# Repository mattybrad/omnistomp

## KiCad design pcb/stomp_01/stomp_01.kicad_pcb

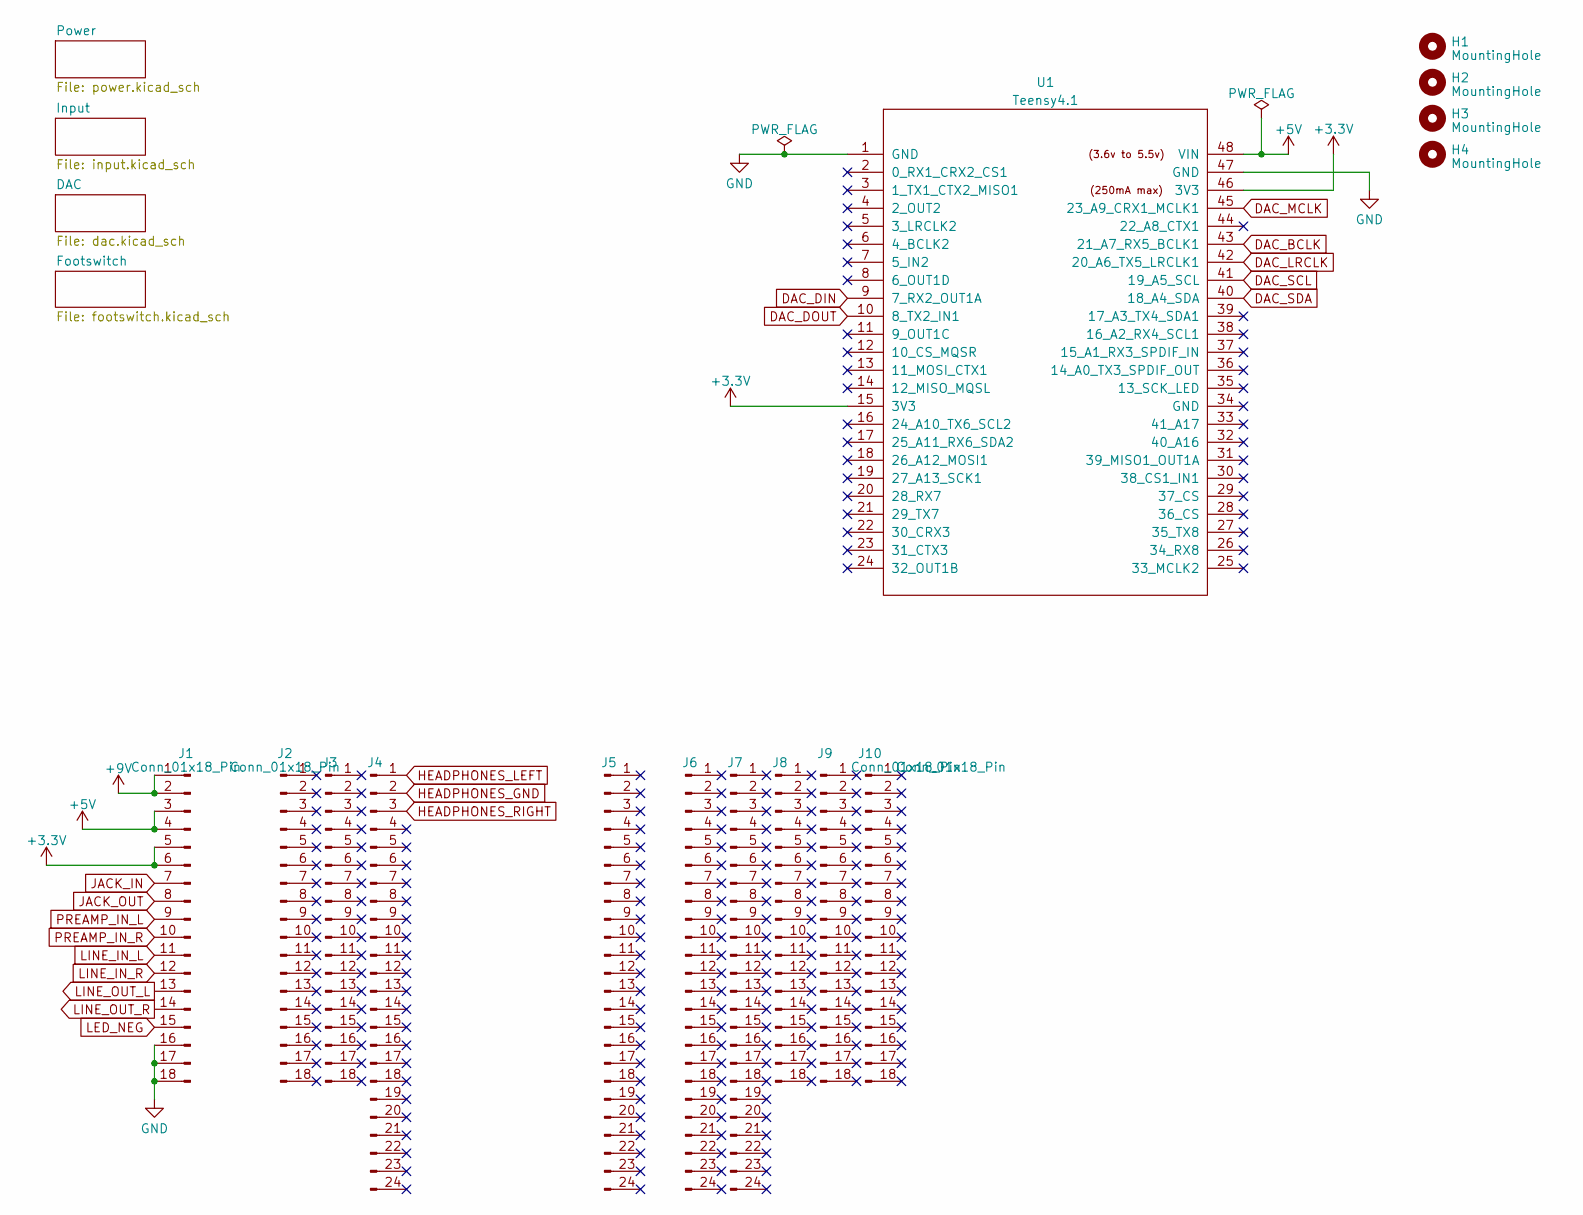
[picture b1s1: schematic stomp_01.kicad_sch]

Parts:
H1, H2, H3, H4: MountingHole; MountingHole_3.2mm_M3
J1, J2, J3, J8, J9, J10: Conn_01x18_Pin; PinHeader_1x18_P2.54mm_Vertical_perf
J4, J5, J6, J7: Conn_01x18_Pin; PinHeader_1x24_P2.54mm_Vertical_perf
U1: Teensy4.1; Teensy41_stomp

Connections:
+3.3V: J1.5, J1.6, U1.15 (3V3), U1.46 (3V3); also elsewhere on the board
+5V: J1.3, J1.4, U1.48 (VIN); also elsewhere on the board
+9V: J1.1, J1.2; also elsewhere on the board
DAC_BCLK: U1.43 (21_A7_RX5_BCLK1); also elsewhere on the board
DAC_DIN: U1.9 (7_RX2_OUT1A); also elsewhere on the board
DAC_DOUT: U1.10 (8_TX2_IN1); also elsewhere on the board
DAC_LRCLK: U1.42 (20_A6_TX5_LRCLK1); also elsewhere on the board
DAC_MCLK: U1.45 (23_A9_CRX1_MCLK1); also elsewhere on the board
DAC_SCL: U1.41 (19_A5_SCL); also elsewhere on the board
DAC_SDA: U1.40 (18_A4_SDA); also elsewhere on the board
GND: J1.16, J1.17, J1.18, U1.1 (GND), U1.47 (GND); also elsewhere on the board
HEADPHONES_GND: J4.2; also elsewhere on the board
HEADPHONES_LEFT: J4.1; also elsewhere on the board
HEADPHONES_RIGHT: J4.3; also elsewhere on the board
JACK_IN: J1.7; also elsewhere on the board
JACK_OUT: J1.8; also elsewhere on the board
LED_NEG: J1.15; also elsewhere on the board
LINE_IN_L: J1.11; also elsewhere on the board
LINE_IN_R: J1.12; also elsewhere on the board
LINE_OUT_L: J1.13; also elsewhere on the board
LINE_OUT_R: J1.14; also elsewhere on the board
PREAMP_IN_L: J1.9; also elsewhere on the board
PREAMP_IN_R: J1.10; also elsewhere on the board

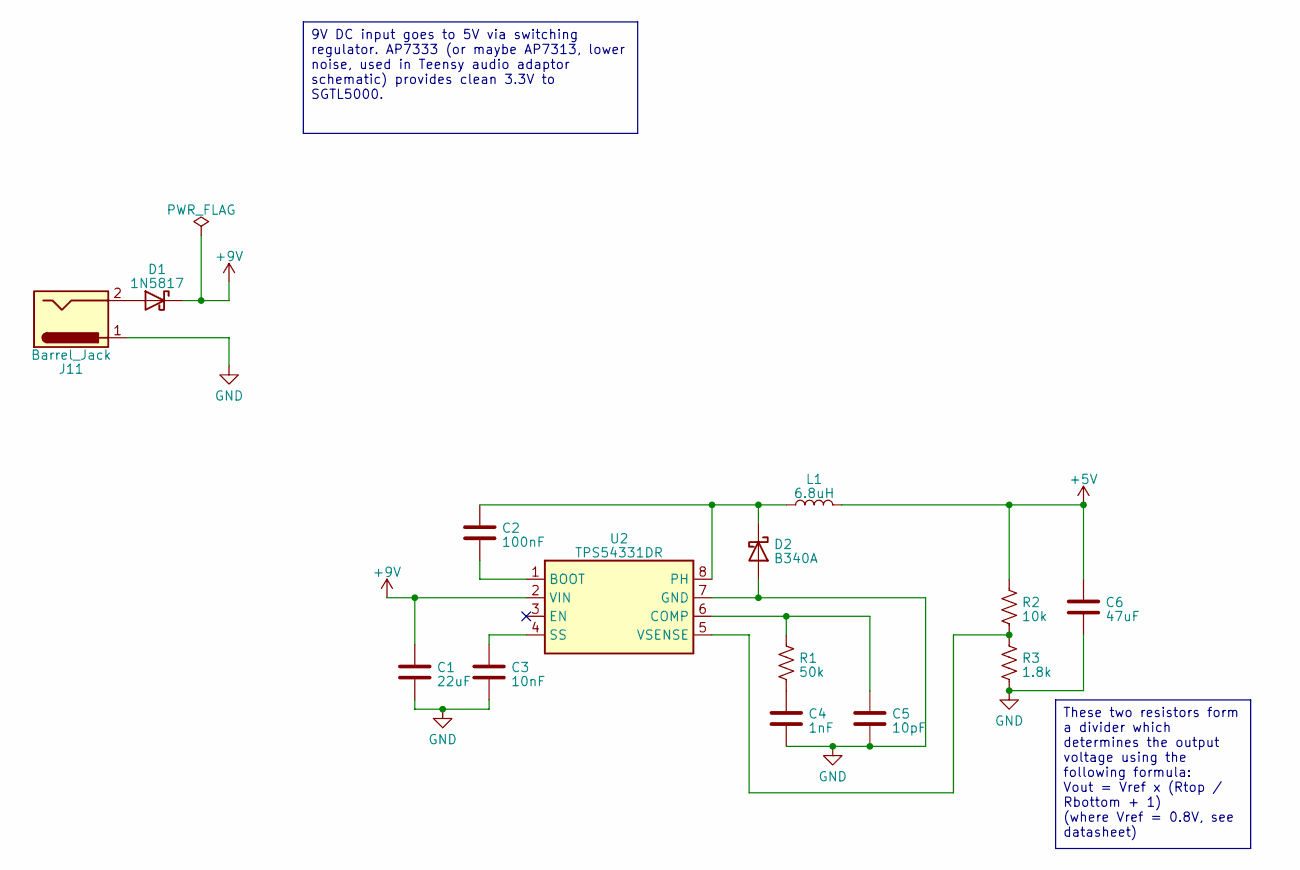
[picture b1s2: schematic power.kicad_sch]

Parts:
C1: 22uF; C_0805_2012Metric
C2: 100nF; C_0603_1608Metric
C3: 10nF; C_0603_1608Metric
C4: 1nF; C_0603_1608Metric
C5: 10pF; C_0603_1608Metric
C6: 47uF; C_1210_3225Metric
D1: 1N5817; D_DO-41_SOD81_P10.16mm_Horizontal
D2: B340A; D_SMA
J11: Barrel_Jack; SolderWire-1sqmm_1x02_P5.4mm_D1.4mm_OD2.7mm
L1: 6.8uH; L_Sunlord_SWPA6045S
R1: 50k; R_0603_1608Metric
R2: 10k; R_0603_1608Metric
R3: 1.8k; R_0603_1608Metric
U2: TPS54331DR; SOIC-8_3.9x4.9mm_P1.27mm

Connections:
+5V: C6.1, L1.2, R2.1; also elsewhere on the board
+9V: C1.1, D1.1 (K), U2.2 (VIN); also elsewhere on the board
GND: C1.2, C3.2, C4.2, C5.2, C6.2, D2.2 (A), J11.1, R3.2, U2.7 (GND); also elsewhere on the board
unnamed: C4.1, R1.2
unnamed: D1.2 (A), J11.2
unnamed: C2.1, D2.1 (K), L1.1, U2.8 (PH)
unnamed: C2.2, U2.1 (BOOT)
unnamed: C5.1, R1.1, U2.6 (COMP)
unnamed: C3.1, U2.4 (SS)
unnamed: R2.2, R3.1, U2.5 (VSENSE)

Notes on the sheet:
9V DC input goes to 5V via switching regulator. AP7333 (or maybe AP7313, lower noise, used in Teensy audio adaptor schematic) provides clean 3.3V to SGTL5000.
These two resistors form a divider which determines the output voltage using the following formula: Vout = Vref x (Rtop / Rbottom + 1) (where Vref = 0.8V, see datasheet)

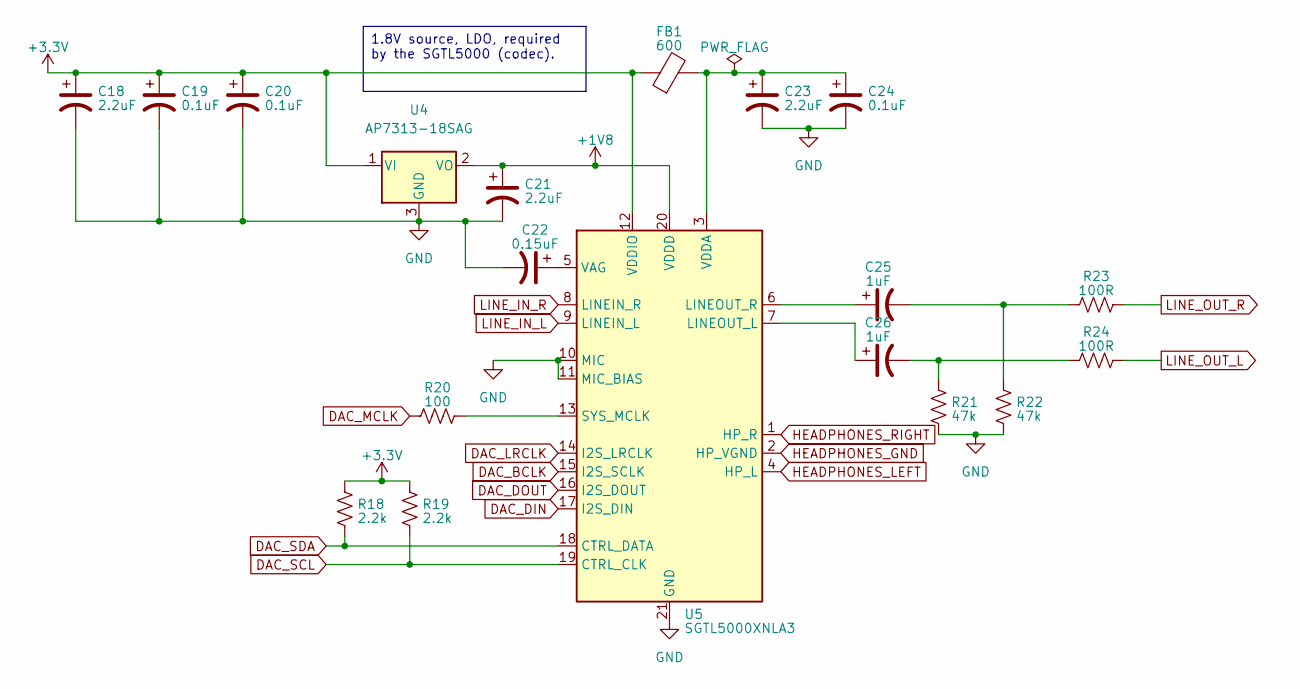
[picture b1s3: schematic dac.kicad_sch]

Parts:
C18, C21, C23: 2.2uF; C_0603_1608Metric
C19, C20, C24: 0.1uF; C_0603_1608Metric
C22: 0.15uF; C_0603_1608Metric
C25, C26: 1uF; C_0603_1608Metric
FB1: 600; L_0603_1608Metric
R18, R19: 2.2k; R_0603_1608Metric
R20: 100; R_0603_1608Metric
R21, R22: 47k; R_0603_1608Metric
R23, R24: 100R; R_0603_1608Metric
U4: AP7313-18SAG; SOT-23
U5: SGTL5000XNLA3; QFN-20-1EP_3x3mm_P0.4mm_EP1.65x1.65mm

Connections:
+1V8: C21.1, U4.2 (VO), U5.20 (VDDD)
+3.3V: C18.1, C19.1, C20.1, FB1.1, R18.2, R19.2, U4.1 (VI), U5.12 (VDDIO); also elsewhere on the board
DAC_BCLK: U5.15 (I2S_SCLK); also elsewhere on the board
DAC_DIN: U5.17 (I2S_DIN); also elsewhere on the board
DAC_DOUT: U5.16 (I2S_DOUT); also elsewhere on the board
DAC_LRCLK: U5.14 (I2S_LRCLK); also elsewhere on the board
DAC_MCLK: R20.2; also elsewhere on the board
DAC_SCL: R19.1, U5.19 (CTRL_CLK); also elsewhere on the board
DAC_SDA: R18.1, U5.18 (CTRL_DATA); also elsewhere on the board
GND: C18.2, C19.2, C20.2, C21.2, C22.2, C23.2, C24.2, R21.1, R22.1, U4.3 (GND), U5.10 (MIC), U5.11 (MIC_BIAS), U5.21 (GND); also elsewhere on the board
HEADPHONES_GND: U5.2 (HP_VGND); also elsewhere on the board
HEADPHONES_LEFT: U5.4 (HP_L); also elsewhere on the board
HEADPHONES_RIGHT: U5.1 (HP_R); also elsewhere on the board
LINE_IN_L: U5.9 (LINEIN_L); also elsewhere on the board
LINE_IN_R: U5.8 (LINEIN_R); also elsewhere on the board
LINE_OUT_L: R24.1; also elsewhere on the board
LINE_OUT_R: R23.1; also elsewhere on the board
unnamed: C25.2, R22.2, R23.2
unnamed: C26.2, R21.2, R24.2
unnamed: C26.1, U5.7 (LINEOUT_L)
unnamed: C25.1, U5.6 (LINEOUT_R)
unnamed: R20.1, U5.13 (SYS_MCLK)
unnamed: C22.1, U5.5 (VAG)
unnamed: C23.1, C24.1, FB1.2, U5.3 (VDDA)

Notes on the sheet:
1.8V source, LDO, required by the SGTL5000 (codec).

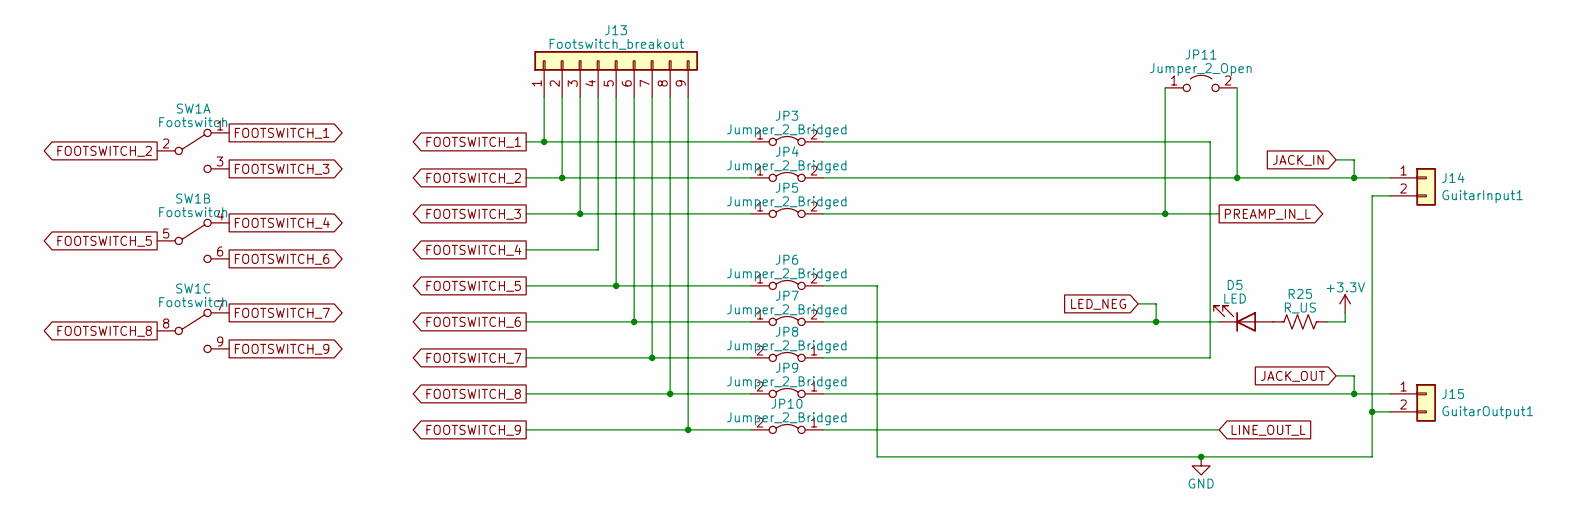
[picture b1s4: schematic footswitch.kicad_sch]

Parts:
D5: LED; LED_D5.0mm
J13: Footswitch_breakout; PinHeader_3x03_P2.54mm_Vertical_footswitch_breakout
J14: GuitarInput1; SolderWire-1sqmm_1x02_P5.4mm_D1.4mm_OD2.7mm
J15: GuitarOutput1; SolderWire-1sqmm_1x02_P5.4mm_D1.4mm_OD2.7mm
JP3, JP4, JP5, JP6, JP7, JP8, JP9, JP10: Jumper_2_Bridged; SolderJumper-2_P1.3mm_Bridged2Bar_RoundedPad1.0x1.5mm
JP11: Jumper_2_Open; SolderJumper-2_P1.3mm_Open_RoundedPad1.0x1.5mm
R25: R_US; R_Axial_DIN0207_L6.3mm_D2.5mm_P7.62mm_Horizontal
SW1: Footswitch; Footswitch_3PDT

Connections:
+3.3V: R25.2; also elsewhere on the board
FOOTSWITCH_1: J13.1, JP3.1 (A), SW1.1 (A)
FOOTSWITCH_2: J13.2, JP4.1 (A), SW1.2 (B)
FOOTSWITCH_3: J13.3, JP5.1 (A), SW1.3 (C)
FOOTSWITCH_4: J13.4, SW1.4 (A)
FOOTSWITCH_5: J13.5, JP6.1 (A), SW1.5 (B)
FOOTSWITCH_6: J13.6, JP7.1 (A), SW1.6 (C)
FOOTSWITCH_7: J13.7, JP8.2 (B), SW1.7 (A)
FOOTSWITCH_8: J13.8, JP9.2 (B), SW1.8 (B)
FOOTSWITCH_9: J13.9, JP10.2 (B), SW1.9 (C)
GND: J14.2, J15.2, JP6.2 (B); also elsewhere on the board
JACK_IN: J14.1, JP4.2 (B), JP11.2 (B); also elsewhere on the board
JACK_OUT: J15.1, JP9.1 (A); also elsewhere on the board
LED_NEG: D5.1 (K), JP7.2 (B); also elsewhere on the board
LINE_OUT_L: JP10.1 (A); also elsewhere on the board
unnamed: D5.2 (A), R25.1
unnamed: JP3.2 (B), JP8.1 (A)
PREAMP_IN_L: JP5.2 (B), JP11.1 (A); also elsewhere on the board

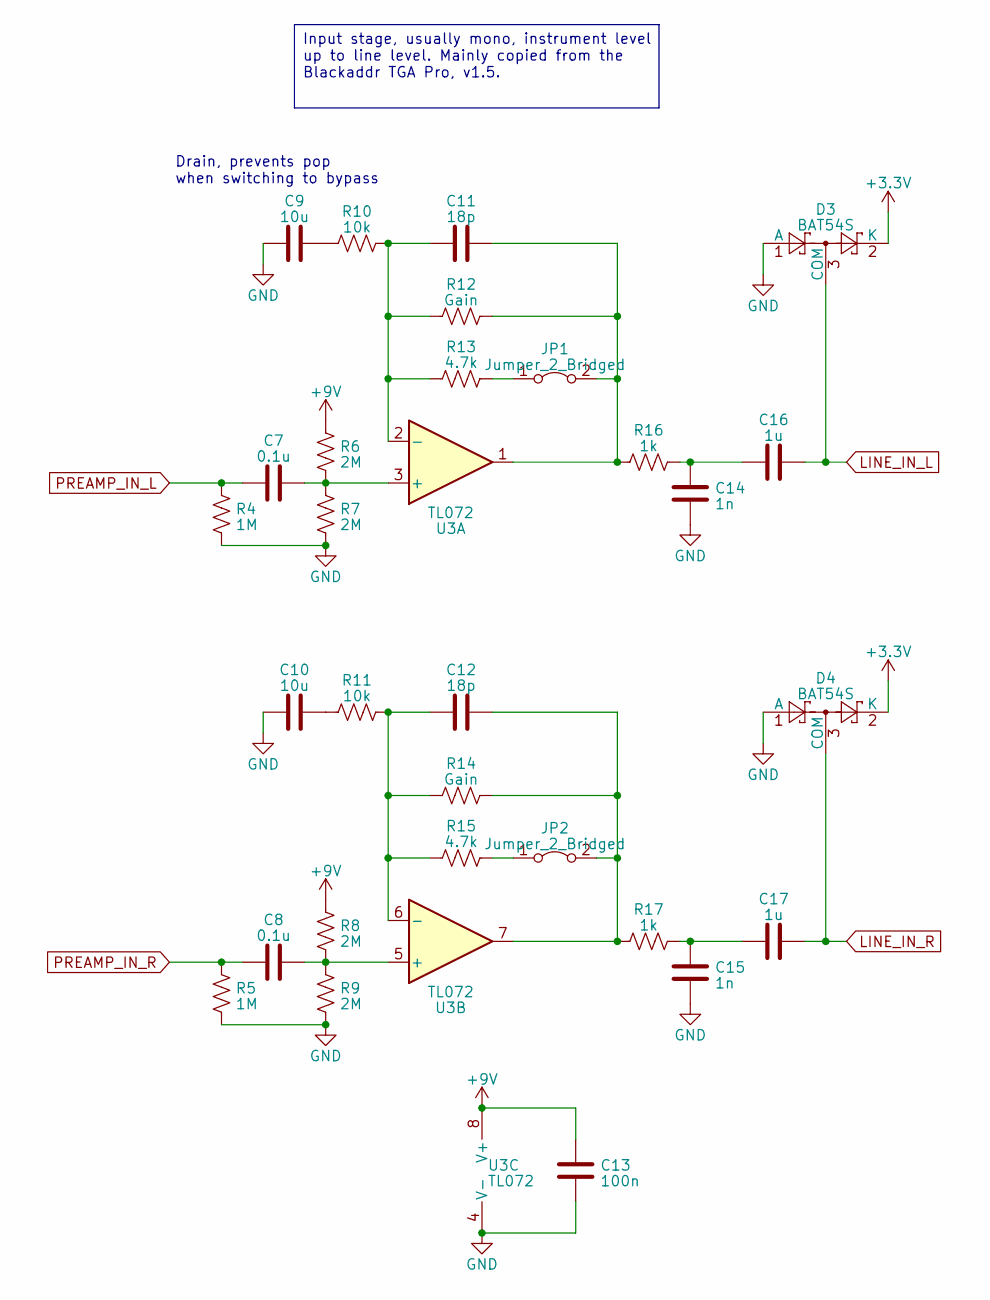
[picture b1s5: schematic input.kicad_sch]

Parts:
C7, C8: 0.1u; C_0603_1608Metric
C9, C10: 10u; C_0603_1608Metric
C11, C12: 18p; C_0603_1608Metric
C13: 100n; C_0603_1608Metric
C14, C15: 1n; C_0603_1608Metric
C16, C17: 1u; C_0603_1608Metric
D3, D4: BAT54S; SOT-23
JP1, JP2: Jumper_2_Bridged; SolderJumper-2_P1.3mm_Bridged2Bar_RoundedPad1.0x1.5mm
R4, R5: 1M; R_0603_1608Metric
R6, R7, R8, R9: 2M; R_0603_1608Metric
R10, R11: 10k; R_0603_1608Metric
R12, R14: Gain; R_Axial_DIN0207_L6.3mm_D2.5mm_P7.62mm_Horizontal
R13, R15: 4.7k; R_0603_1608Metric
R16, R17: 1k; R_0603_1608Metric
U3: TL072; SOIC-8_3.9x4.9mm_P1.27mm

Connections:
+3.3V: D3.2 (K), D4.2 (K); also elsewhere on the board
+9V: C13.2, R6.1, R8.1, U3.8 (V+); also elsewhere on the board
GND: C9.1, C10.1, C13.1, C14.2, C15.2, D3.1 (A), D4.1 (A), R4.2, R5.2, R7.2, R9.2, U3.4 (V-); also elsewhere on the board
LINE_IN_L: C16.1, D3.3 (COM); also elsewhere on the board
LINE_IN_R: C17.1, D4.3 (COM); also elsewhere on the board
unnamed: C9.2, R10.1
unnamed: C10.2, R11.1
unnamed: C14.1, C16.2, R16.2
unnamed: C15.1, C17.2, R17.2
unnamed: JP1.1 (A), R13.2
unnamed: C11.2, JP1.2 (B), R12.2, R16.1, U3.1
unnamed: JP2.1 (A), R15.2
unnamed: C12.2, JP2.2 (B), R14.2, R17.1, U3.7
unnamed: C7.2, R6.2, R7.1, U3.3 (+)
unnamed: C11.1, R10.2, R12.1, R13.1, U3.2 (-)
unnamed: C8.2, R8.2, R9.1, U3.5 (+)
unnamed: C12.1, R11.2, R14.1, R15.1, U3.6 (-)
PREAMP_IN_L: C7.1, R4.1; also elsewhere on the board
PREAMP_IN_R: C8.1, R5.1; also elsewhere on the board

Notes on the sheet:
Drain, prevents pop when switching to bypass
Input stage, usually mono, instrument level up to line level. Mainly copied from the Blackaddr TGA Pro, v1.5.

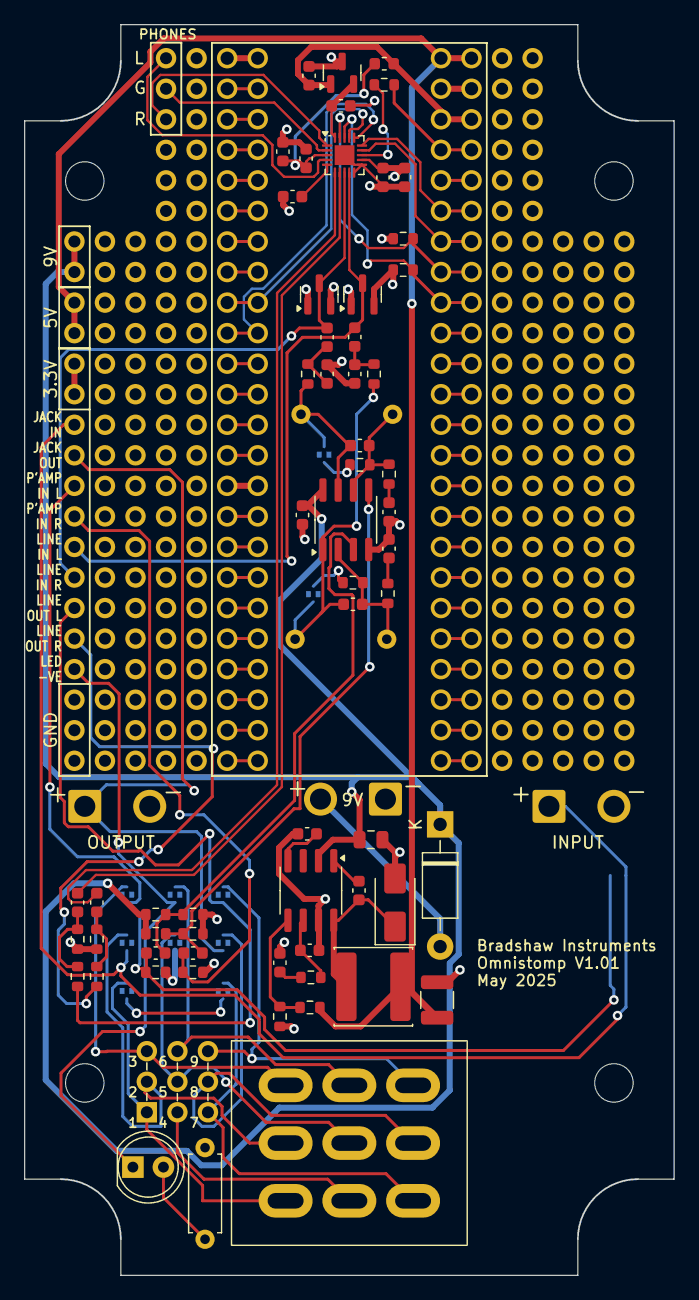
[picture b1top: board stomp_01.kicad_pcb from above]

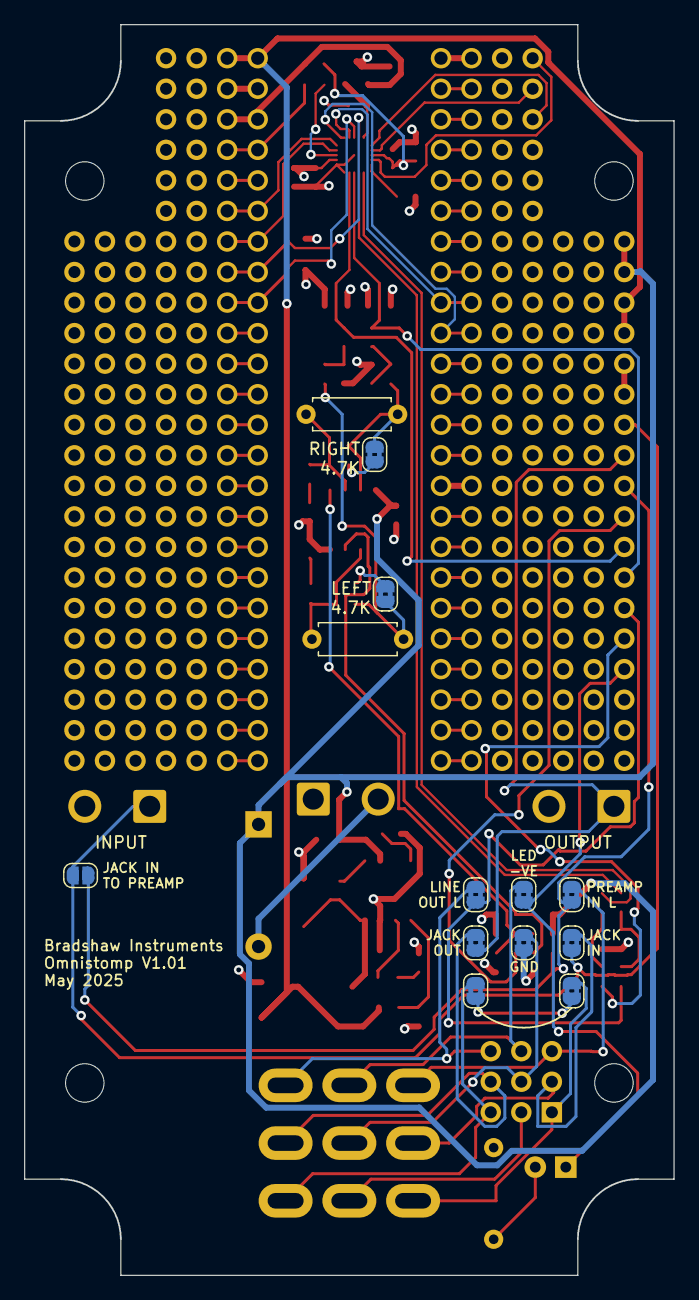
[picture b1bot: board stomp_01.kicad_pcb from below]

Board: 4 copper layers, 54.0 x 104.0 mm, 93 parts (13 on the bottom side), 61 nets.

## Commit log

2023-09-06 early schematic stuff
2025-01-13 came back to the project
2025-01-13 more sheets
2025-01-13 adding all the components...
2025-01-15 not much
2025-01-15 freecad stuff
2025-01-16 taking shape...
2025-01-16 teensy footprint
2025-01-16 seeing whether everything will fit...
2025-01-16 input stage schematic
2025-01-16 more input stage faffing
2025-01-17 better layout in enclosure
2025-01-18 good progress with physical layout
2025-01-19 footswitch routing
2025-01-20 pcb...
2025-01-20 tweaking layout, issue with usb socket placement
2025-01-21 9v power stuff
2025-01-21 changed voltage regulator
2025-01-21 adding perfboard section
2025-01-22 tidying up footprints, layout, etc
2025-01-22 tidying up dac connections
2025-01-24 layout getting closer
2025-01-28 fixing ERC stuff, importing PCB into freecad
2025-01-28 save before routing
2025-01-28 <50 unrouted...
2025-01-29 7 unrouted...
2025-01-29 passed ERC!
2025-02-17 pcb done
2025-05-20 where does everything go
2025-05-20 more tweaks
2025-05-20 looking nice
2025-05-21 pre routing
2025-05-21 100 unrouted
2025-05-21 53 unrouted
2025-05-21 zero unrouted
2025-05-21 pcb v1.01 done
